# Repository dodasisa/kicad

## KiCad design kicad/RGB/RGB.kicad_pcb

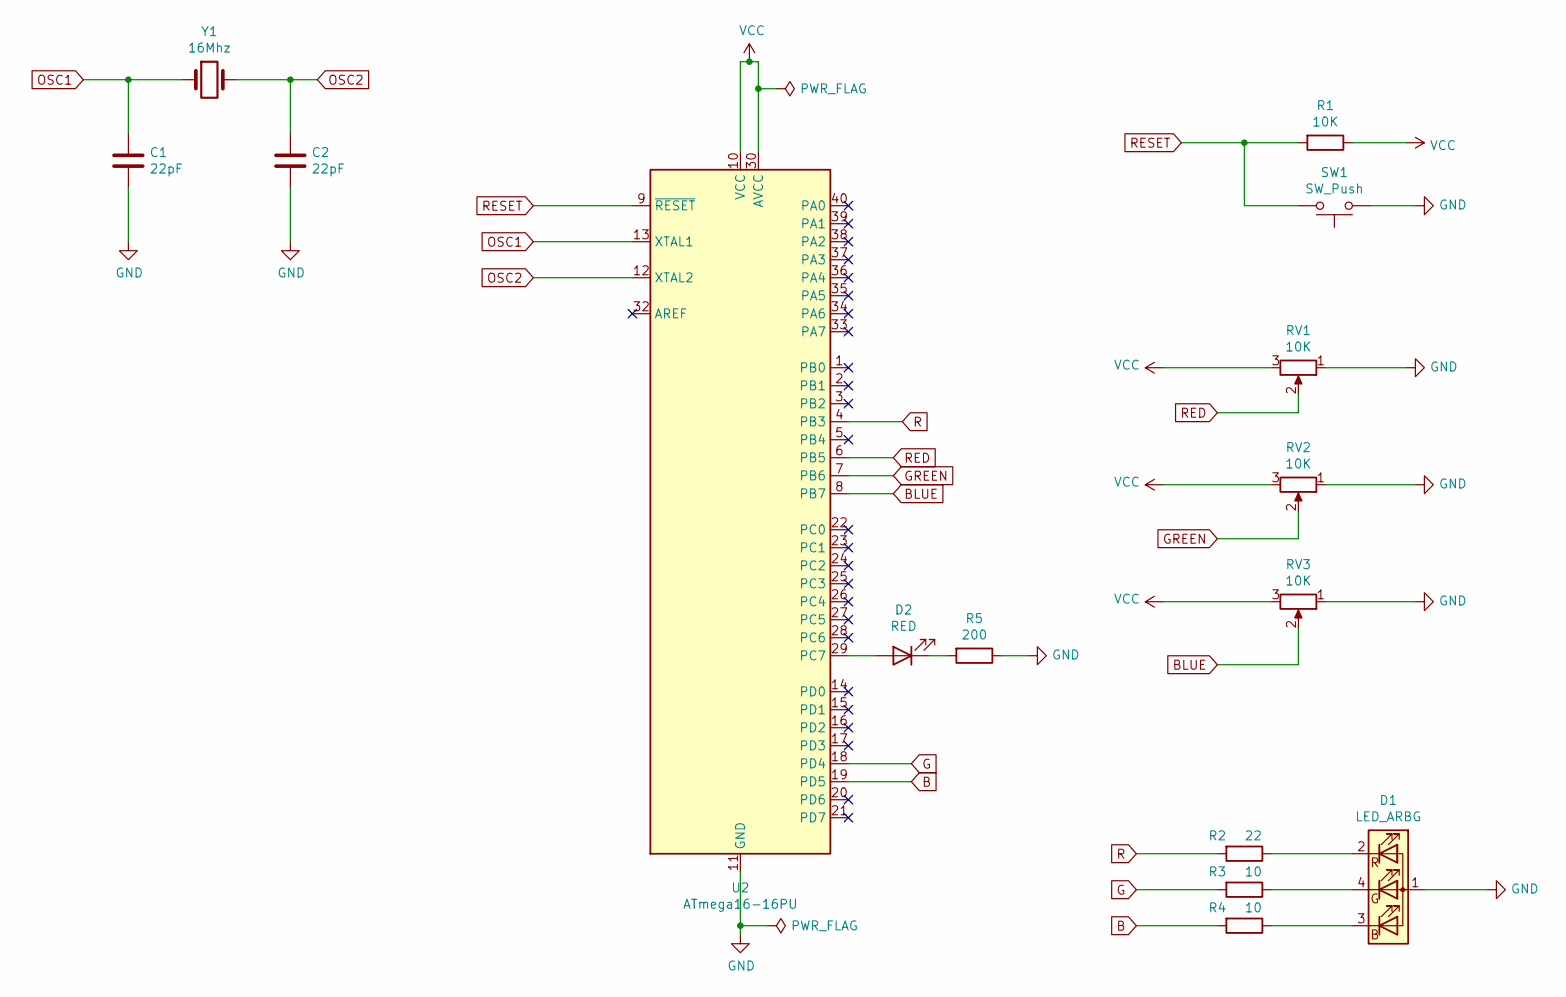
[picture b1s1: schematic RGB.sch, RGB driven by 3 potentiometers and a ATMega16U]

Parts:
C1, C2: 22pF; C_Disc_D3.0mm_W1.6mm_P2.50mm
D1: LED_ARBG; LED_D5.0mm-4_RGB
D2: RED; LED_D3.0mm
R1: 10K; R_Axial_DIN0309_L9.0mm_D3.2mm_P12.70mm_Horizontal
R2: 22; R_Axial_DIN0309_L9.0mm_D3.2mm_P12.70mm_Horizontal
R3, R4: 10; R_Axial_DIN0309_L9.0mm_D3.2mm_P12.70mm_Horizontal
R5: 200; R_Axial_DIN0309_L9.0mm_D3.2mm_P12.70mm_Horizontal
RV1, RV2, RV3: 10K; Potentiometer_ACP_CA9-V10_Vertical
SW1: SW_Push; Push_E-Switch_KS01Q01
U2: ATmega16-16PU; DIP-40_W15.24mm
Y1: 16Mhz; Crystal_AT310_D3.0mm_L10.0mm_Horizontal

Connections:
B: R4.2, U2.19 (PD5)
BLUE: RV3.2, U2.8 (PB7)
G: R3.2, U2.18 (PD4)
GND: C1.2, C2.2, D1.1 (A), R5.1, RV1.1, RV2.1, RV3.1, SW1.1, U2.11 (GND), U2.31 (GND)
GREEN: RV2.2, U2.7 (PB6)
unnamed: D1.2 (RK), R2.1
unnamed: D1.3 (BK), R4.1
unnamed: D1.4 (GK), R3.1
unnamed: D2.1 (K), R5.2
unnamed: D2.2 (A), U2.29 (PC7)
OSC1: C1.1, U2.13 (XTAL1), Y1.1
OSC2: C2.1, U2.12 (XTAL2), Y1.2
R: R2.2, U2.4 (PB3)
RED: RV1.2, U2.6 (PB5)
RESET: R1.2, SW1.2, U2.9 (~RESET)
VCC: R1.1, RV1.3, RV2.3, RV3.3, U2.10 (VCC), U2.30 (AVCC)

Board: 2 copper layers, 15 parts (0 on the bottom side), 16 nets, no tracks yet.

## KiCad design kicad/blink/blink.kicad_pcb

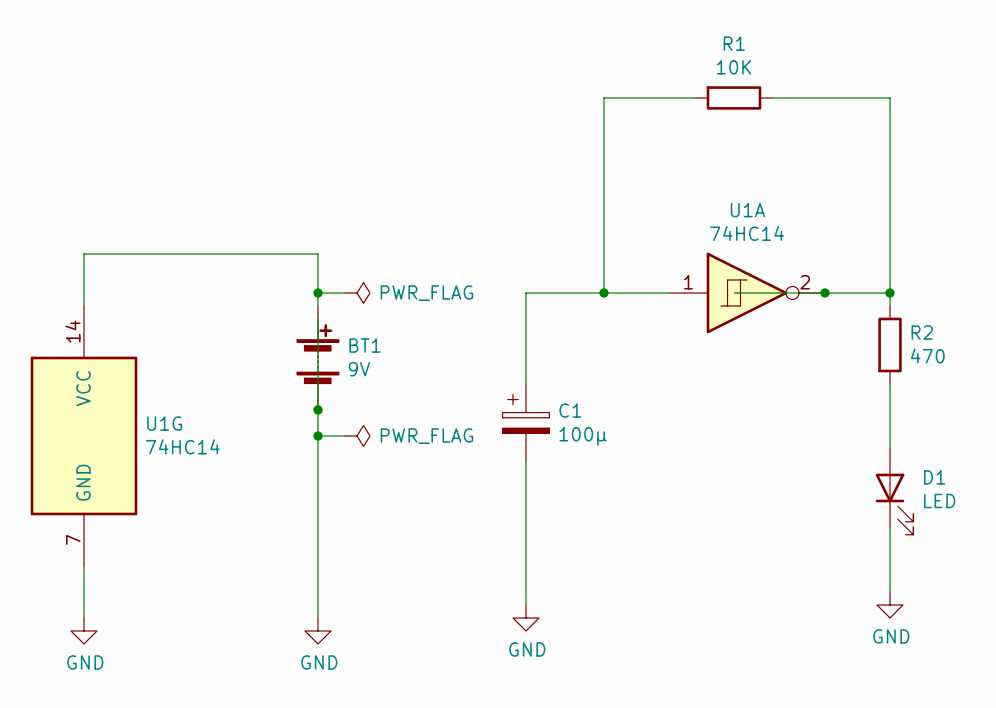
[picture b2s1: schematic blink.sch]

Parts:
BT1: 9V; PinHeader_1x02_P2.54mm_Vertical
C1: 100µ; CP_Radial_D10.0mm_P5.00mm
D1: LED; LED_D5.0mm
R1: 10K; R_Axial_DIN0414_L11.9mm_D4.5mm_P15.24mm_Horizontal
R2: 470; R_Axial_DIN0414_L11.9mm_D4.5mm_P15.24mm_Horizontal
U1: 74HC14; DIP-14_W7.62mm

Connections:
GND: BT1.2 (-), C1.2, D1.1 (K), U1.7 (GND)
unnamed: BT1.1 (+), U1.14 (VCC)
unnamed: C1.1, R1.2, U1.1
unnamed: D1.2 (A), R2.2
unnamed: R1.1, R2.1, U1.2

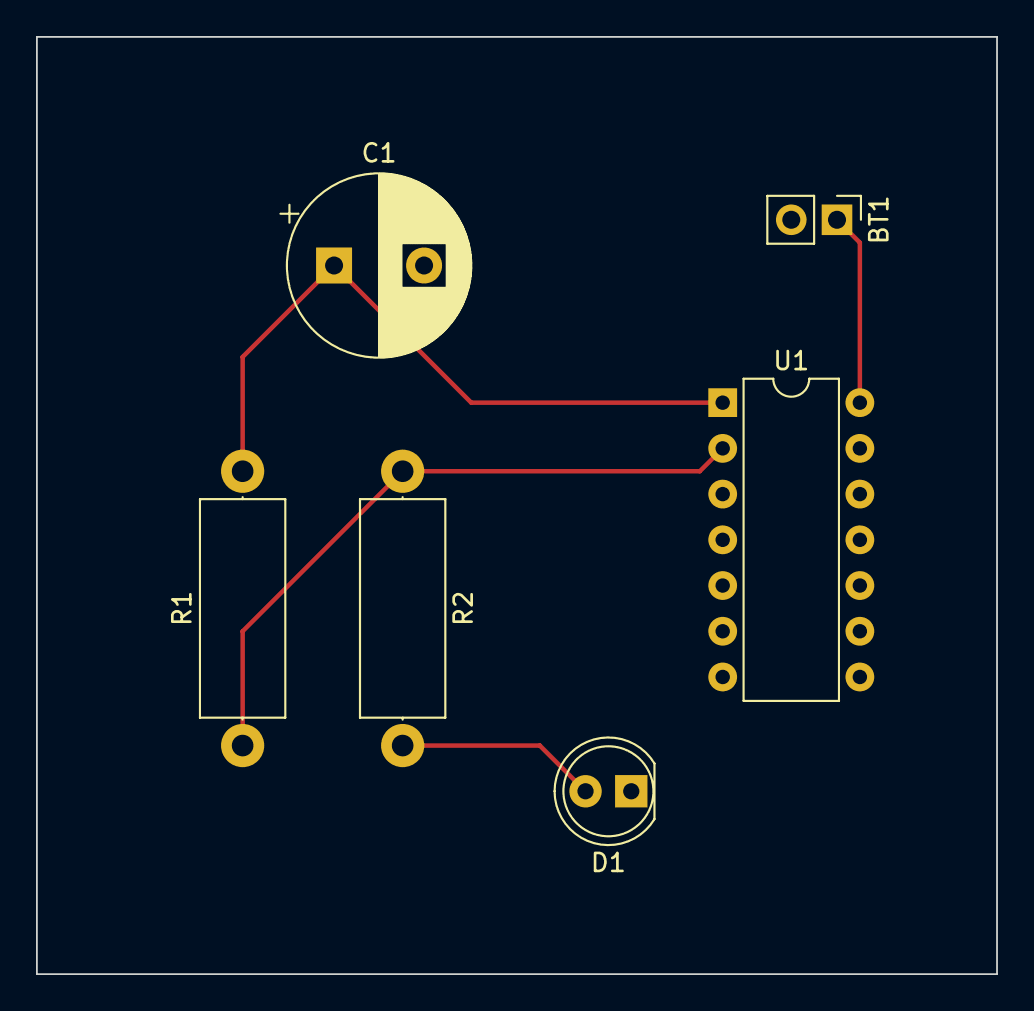
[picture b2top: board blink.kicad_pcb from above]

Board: 2 copper layers, 53.3 x 52.1 mm, 6 parts (0 on the bottom side), 5 nets.

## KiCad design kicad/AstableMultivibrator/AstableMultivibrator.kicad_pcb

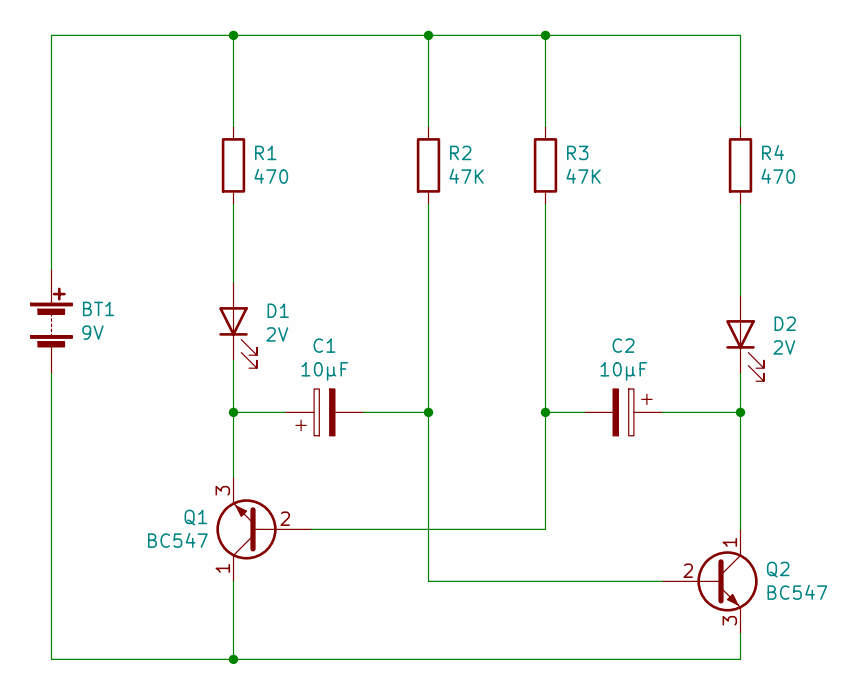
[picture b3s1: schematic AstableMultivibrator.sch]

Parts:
BT1: 9V; SolderWire-0.75sqmm_1x02_P4.8mm_D1.25mm_OD2.3mm
C1, C2: 10µF; CP_Elec_4x3
D1, D2: 2V; LED_0201_0603Metric
Q1, Q2: BC547; TO-92_Inline
R1, R4: 470; R_0201_0603Metric
R2, R3: 47K; R_0201_0603Metric

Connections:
unnamed: BT1.1 (+), R1.1, R2.1, R3.1, R4.1
unnamed: BT1.2 (-), Q1.1 (C), Q2.3 (E)
unnamed: C1.1, D1.1 (K), Q1.3 (E)
unnamed: C1.2, Q2.2 (B), R2.2
unnamed: C2.1, D2.1 (K), Q2.1 (C)
unnamed: C2.2, Q1.2 (B), R3.2
unnamed: D1.2 (A), R1.2
unnamed: D2.2 (A), R4.2

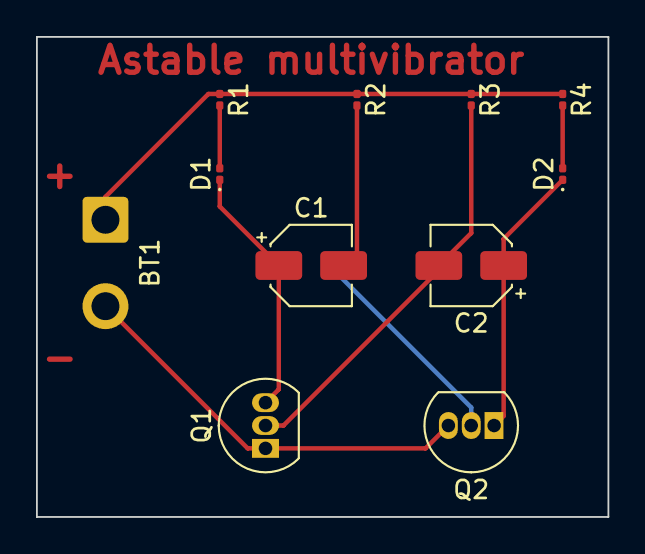
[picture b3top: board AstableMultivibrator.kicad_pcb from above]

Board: 2 copper layers, 31.8 x 26.7 mm, 11 parts (0 on the bottom side), 8 nets.

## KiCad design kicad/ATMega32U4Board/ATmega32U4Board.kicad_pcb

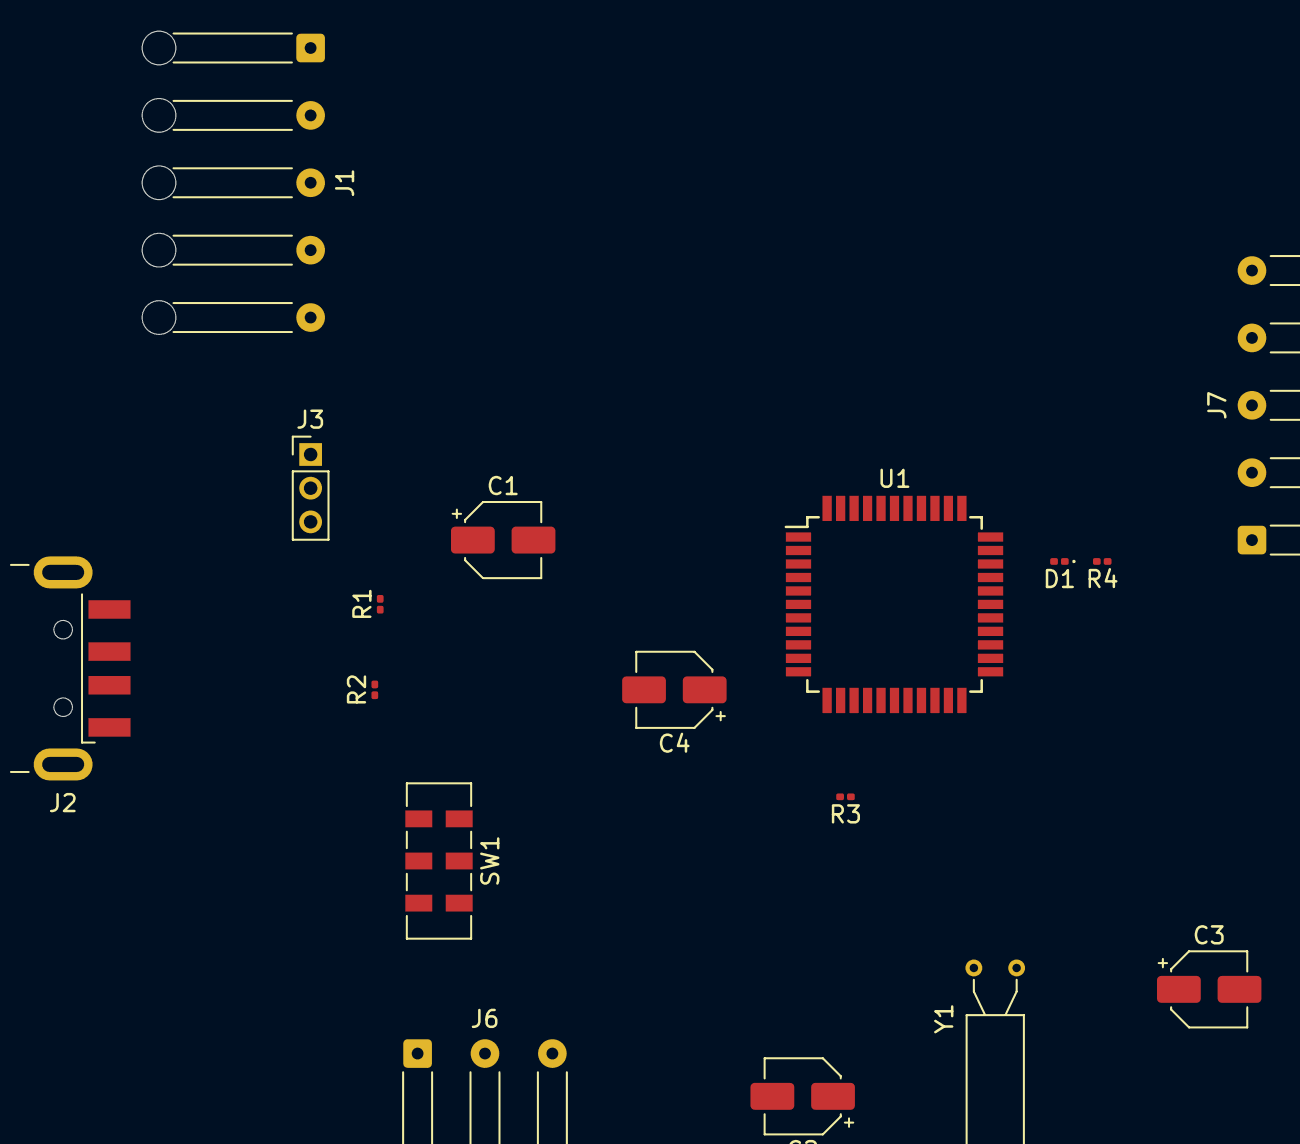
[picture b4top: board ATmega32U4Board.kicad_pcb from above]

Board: 2 copper layers, 17 parts (0 on the bottom side), 18 nets, no tracks yet.

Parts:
C1: 10µF; CP_Elec_4x3
C2, C3: 12-22pF; CP_Elec_4x3
C4: 1µF; CP_Elec_4x3
D1: 1.8V; LED_0201_0603Metric
J1, J7: Conn_01x05_Male; SolderWire-0.15sqmm_1x05_P4mm_D0.5mm_OD1.5mm_Relief
J2: USB_A; USB_A_CNCTech_1001-011-01101_Horizontal
J3: Conn_01x03_Male; PinHeader_1x03_P2.00mm_Vertical
J6: Conn_01x03_Male; SolderWire-0.15sqmm_1x03_P4mm_D0.5mm_OD1.5mm_Relief
R1, R2: 22; R_0201_0603Metric
R3: 10K; R_0201_0603Metric
R4: 200; R_0201_0603Metric
SW1: SW_Push_SPDT; SW_DPDT_CK_JS202011JCQN
U1: ATmega32U4-AU; TQFP-44_10x10mm_P0.8mm
Y1: Crystal; Crystal_AT310_D3.0mm_L10.0mm_Horizontal

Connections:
GND: C1.2, C2.2, C3.2, C4.2, J1.4, J2.4, J2.5, J6.3, J7.4, R4.1, SW1.1, SW1.3, U1.5, U1.15, U1.23, U1.35, U1.43
unnamed: C1.1, J2.1, J3.3, U1.7
unnamed: C2.1, U1.17, Y1.1
unnamed: C3.1, U1.16, Y1.2
unnamed: C4.1, U1.6
unnamed: D1.1, R4.2
unnamed: D1.2, U1.32
unnamed: J1.1, J6.2, J7.1
unnamed: J1.2, J7.2, U1.19
unnamed: J1.3, J7.3, U1.18
unnamed: J1.5, J3.1
unnamed: J2.2, R2.2
unnamed: J2.3, R1.2
unnamed: J6.1, U1.12
unnamed: R1.1, U1.4
unnamed: R2.1, U1.3
unnamed: R3.2, SW1.2, U1.13
VCC: J3.2, J7.5, R3.1, U1.2, U1.14, U1.24, U1.34, U1.44

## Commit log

2021-05-24 First commit of existing projects
2021-05-24 start new project.
2021-05-24 Schema done, values to add
2021-05-24 Values and power led added. Schema done.
2021-05-24 page settings
2021-05-24 Replaced ATMega16-16AU by ATMega16-16PU
2021-05-24 Footprints added
2021-05-24 started PCB
